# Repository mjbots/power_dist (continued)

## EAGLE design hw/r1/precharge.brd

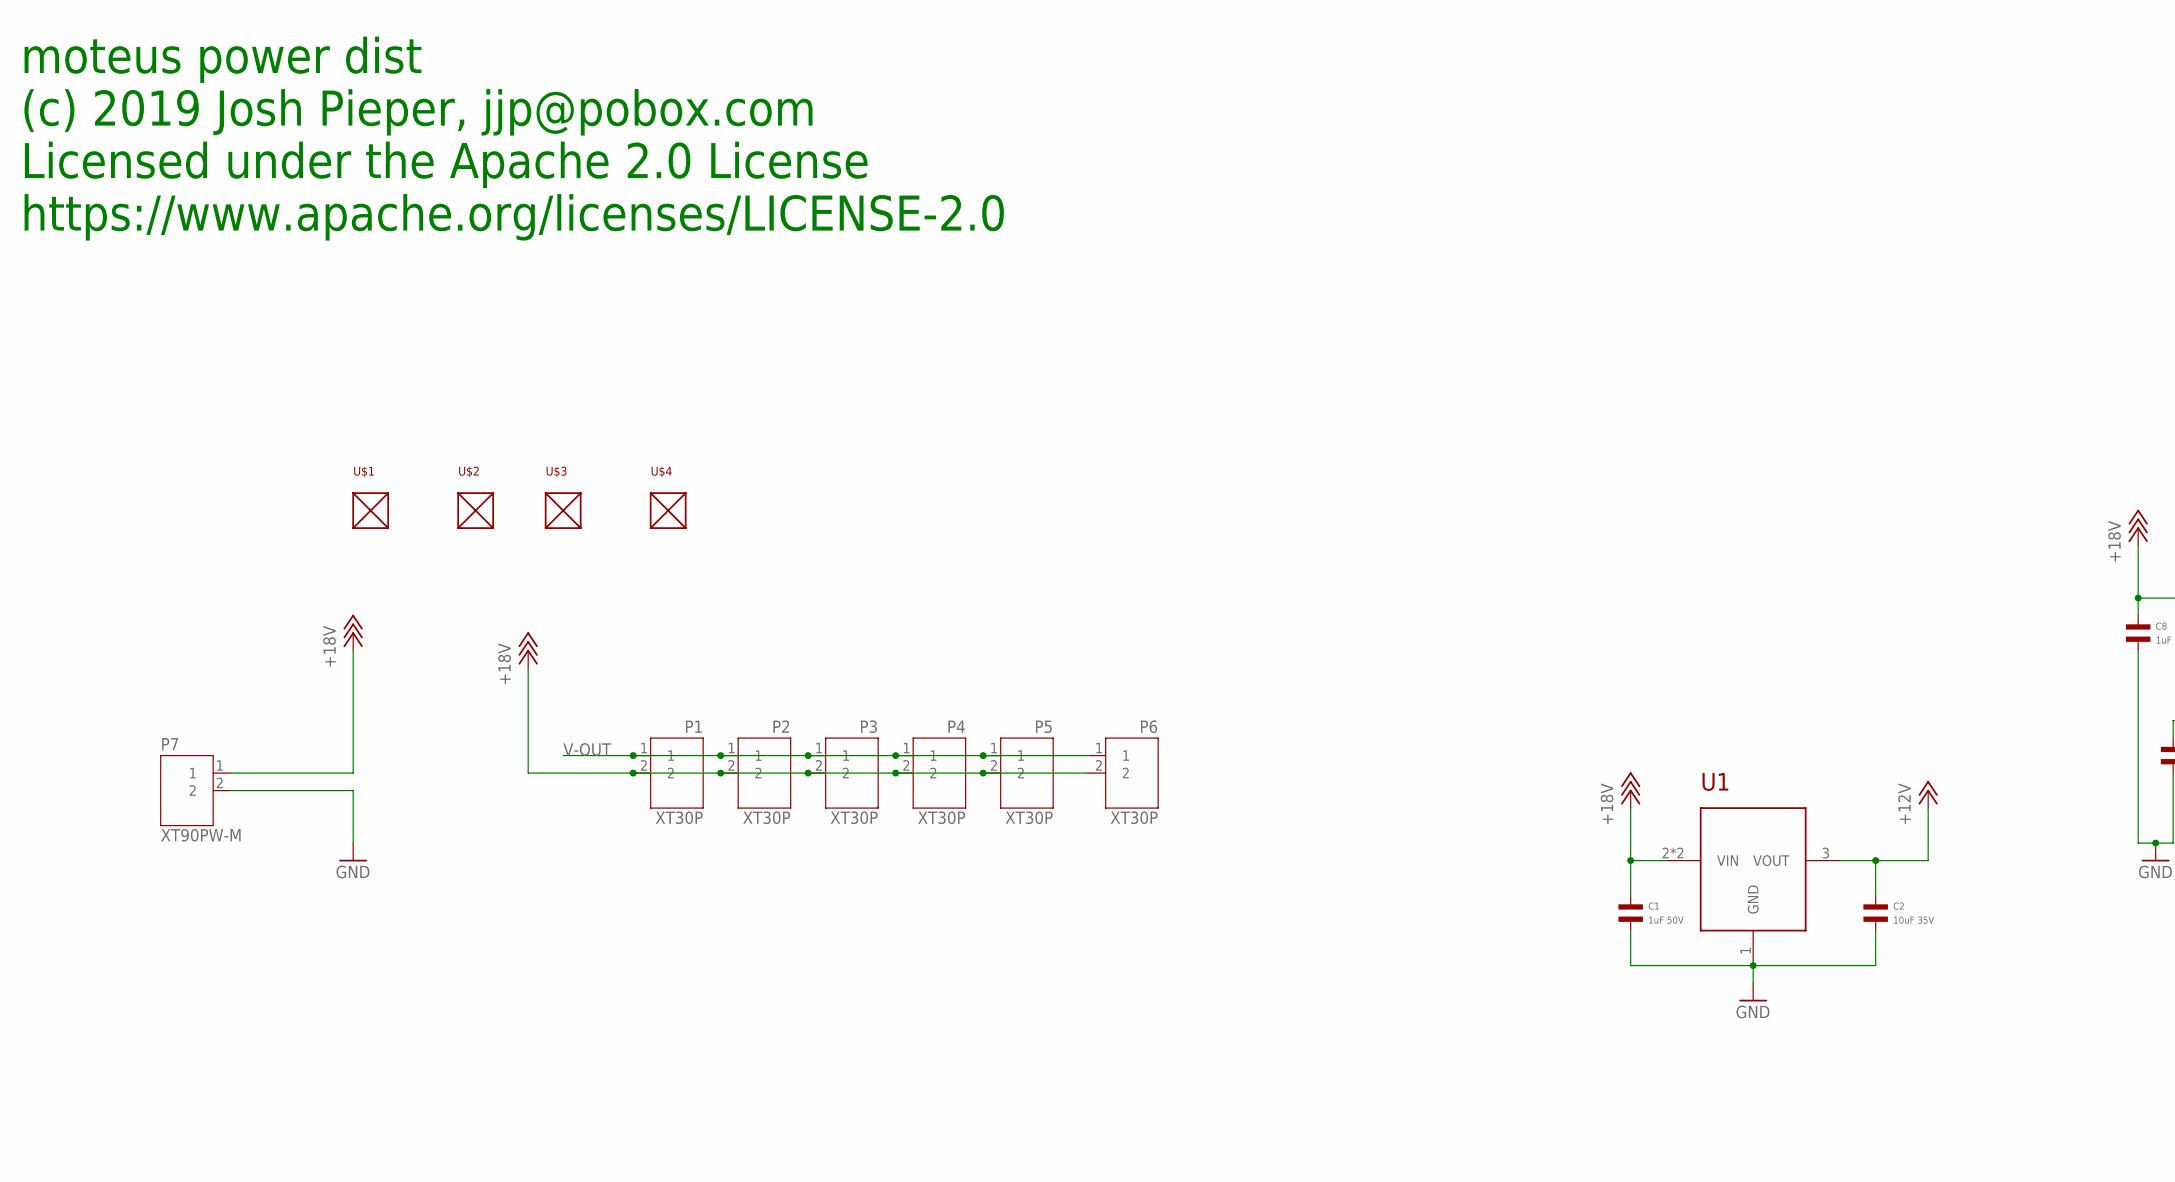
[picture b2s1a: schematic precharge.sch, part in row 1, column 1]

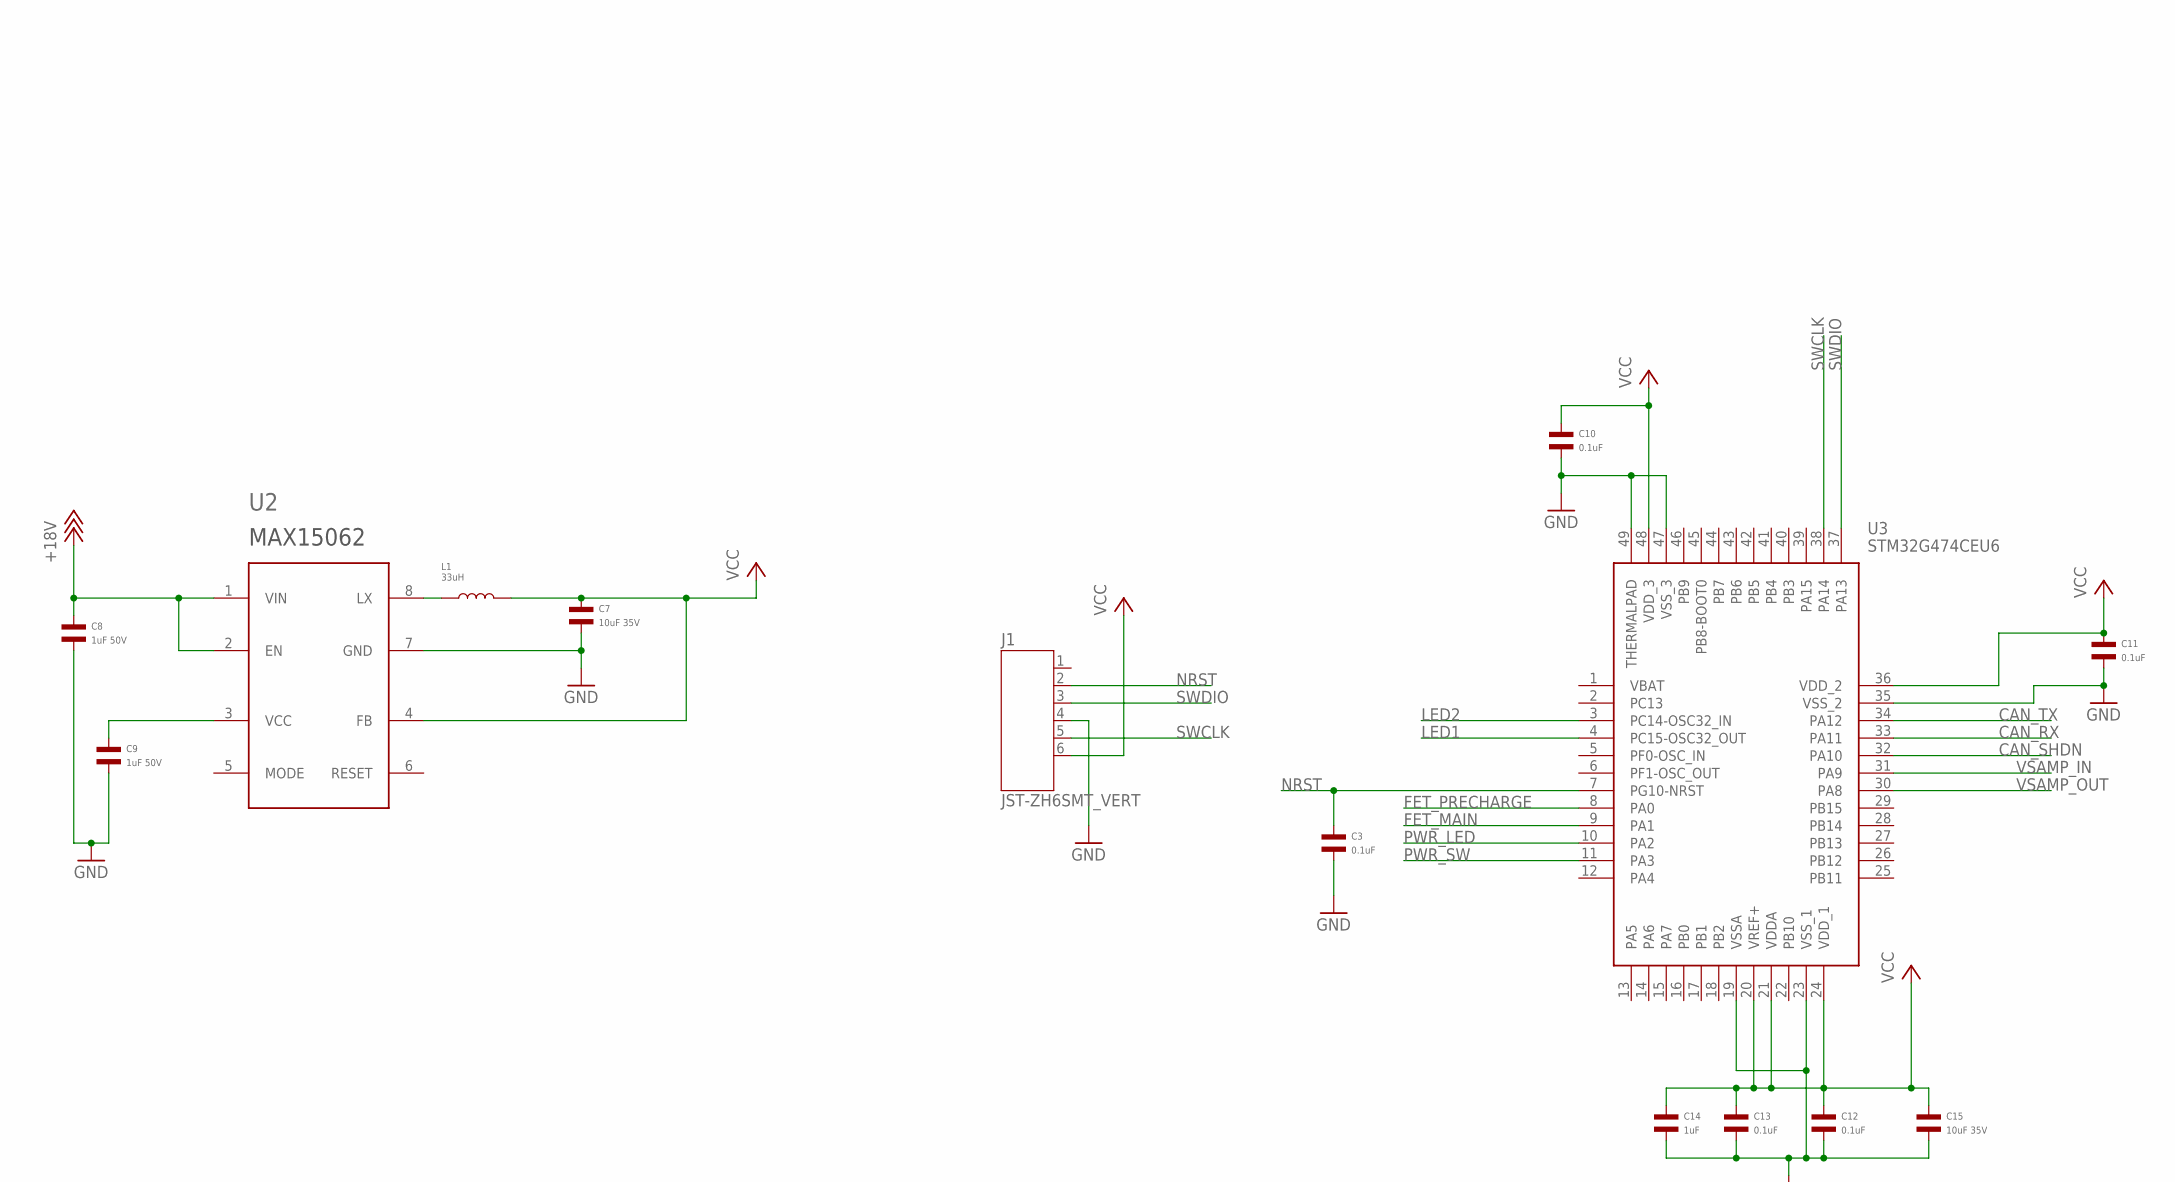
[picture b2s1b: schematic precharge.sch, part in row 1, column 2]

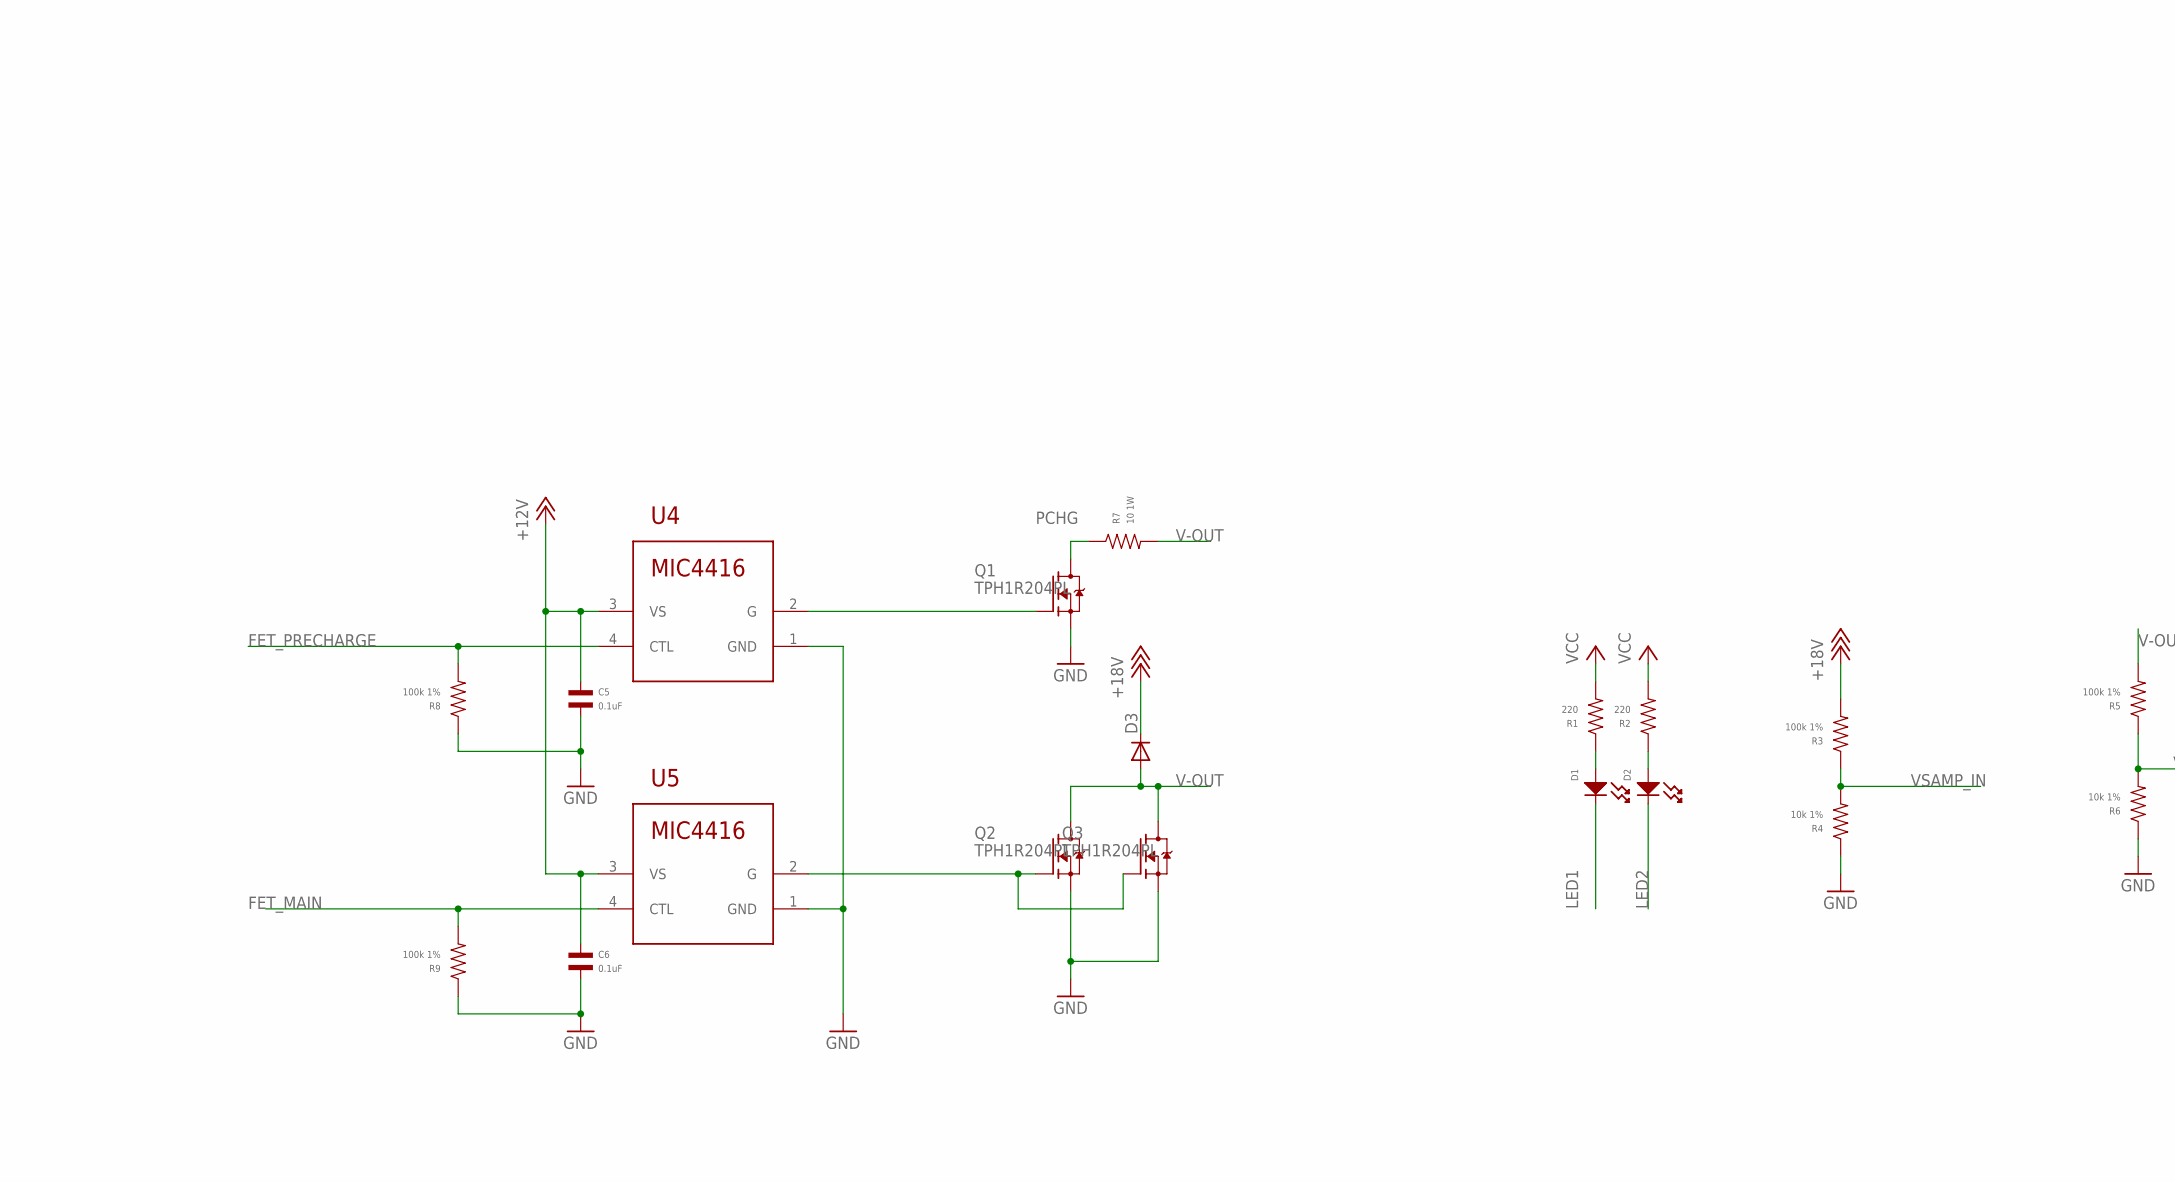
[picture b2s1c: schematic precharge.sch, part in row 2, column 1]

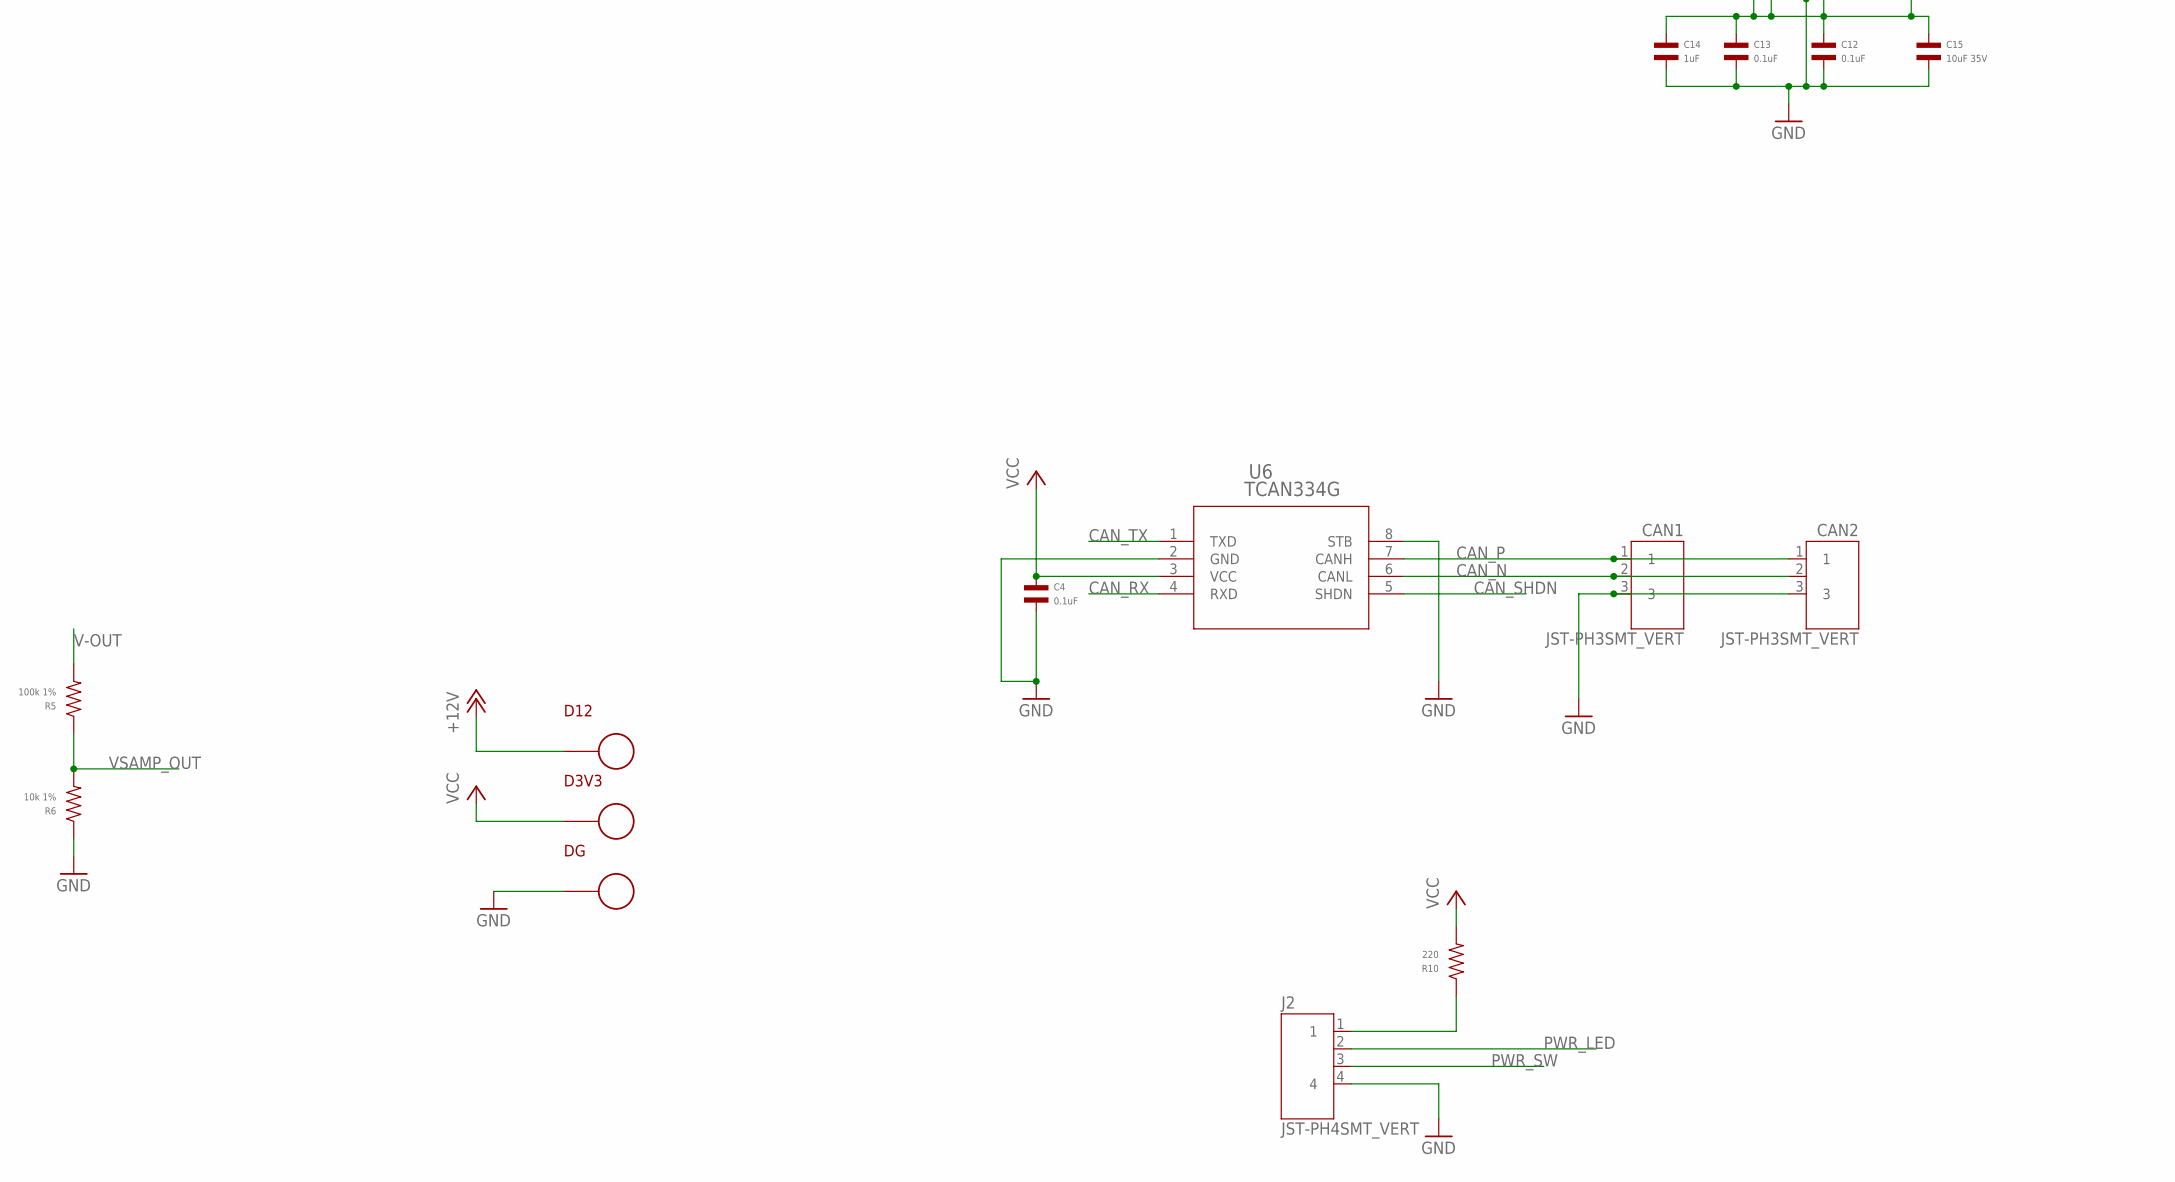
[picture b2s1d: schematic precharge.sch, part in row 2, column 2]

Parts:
C1, C8, C9: 1uF 50V; C0603; MPN CL10A105KB8NNNC
C2, C7, C15: 10uF 35V; C1206; MPN CGA5L1X7R1V106K160AC
C3, C4, C5, C6, C10, C11, C12, C13: 0.1uF; C0402; MPN MF-CAP-0402-0.1uF
C14: 1uF; C0402; MPN MF-CAP-0402-1uF
CAN1, CAN2: JST-PH3SMT_VERT; JST_B3B_PH-SM4-TB(LF)(SN); MPN B3B-PH-SM4-TB(LF)(SN)
D1, D2: LED_SINGLE-0603; LED0603; MPN MF-LED-0603-RED
D3: DIODE-; DO-214AB; MPN SK510L-TP
D3V3, D12: PAD24AWG_PAD; 24AWG_PAD
DG: PAD24AWG_PAD; 24AWG_PAD
J1: JST-ZH6SMT_VERT; JST_B6B-ZR-SM4-TF(LF)(SN); MPN B6B-ZR-SM4-TF(LF)(SN)
J2: JST-PH4SMT_VERT; JST_B4B_PH-SM4-TB(LF)(SN); MPN B4B-PH-SM4-TB(LF)(SN)
L1: 33uH; L1210; MPN NLFV32T-330K-EF
P1, P2, P3, P4, P5, P6: XT30P
P7: XT90PW-M
Q1, Q2, Q3: TPH1R204PL; SOP_ADVANCE; MPN TPH1R204PL,L1Q
R1, R2, R10: 220; R0603; MPN MF-RES-0603-220
R3, R5, R8, R9: 100k 1%; R0603; MPN CRCW0603100KFKEA
R4, R6: 10k 1%; R0603; MPN ERT-J1VG103FA
R7: 10 1W; R1206; MPN HRG3216Q-10R0-D-T1
U1: ZXTR2012Z; SOT89; MPN ZXTR2012Z-13
U2: MAX150628TDFN; 8TDFN; MPN MAX15062AATA+T
U3: STM32G474CEU6; QFN50P700X700X60-49N; MPN STM32G474CEU6
U4, U5: MIC4416; SOT143
U6: TCAN334G; SOT23-8; MPN TCAN334GDR
U$1, U$2, U$3, U$4: MOUNT; M2.5MOUNT

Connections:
+12V: C2.P$1, C5.P$1, C6.P$1, D12.P$1, U1.3 (VOUT), U4.3 (VS), U5.3 (VS)
+18V: C1.P$1, C8.P$1, D3.C, P1.2, P2.2, P3.2, P4.2, P5.2, P6.2, P7.1, R3.P$2, U1.2 (VIN), U1.PAD (VIN), U2.1 (VIN), U2.2 (EN)
CAN_N: CAN1.2, CAN2.2, U6.6 (CANL)
CAN_P: CAN1.1, CAN2.1, U6.7 (CANH)
CAN_RX: U3.33 (PA11), U6.4 (RXD)
CAN_SHDN: U3.32 (PA10), U6.5 (SHDN)
CAN_TX: U3.34 (PA12), U6.1 (TXD)
FET_MAIN: R9.P$2, U3.9 (PA1), U5.4 (CTL)
FET_PRECHARGE: R8.P$2, U3.8 (PA0), U4.4 (CTL)
GND: C1.P$2, C2.P$2, C3.P$2, C4.P$2, C5.P$2, C6.P$2, C7.P$2, C8.P$2, C9.P$2, C10.P$2, C11.P$2, C12.P$2, C13.P$2, C14.P$2, C15.P$2, CAN1.3, CAN2.3, DG.P$1, J1.4, J2.4, P7.2, Q1.1 (S), Q1.2 (S), Q1.3 (S), Q2.1 (S), Q2.2 (S), Q2.3 (S), Q3.1 (S), Q3.2 (S), Q3.3 (S), R4.P$1, R6.P$1, R8.P$1, R9.P$1, U1.1 (GND), U2.7 (GND), U3.19 (VSSA), U3.23 (VSS_1), U3.35 (VSS_2), U3.47 (VSS_3), U3.49 (THERMALPAD), U4.1 (GND), U5.1 (GND), U6.2 (GND), U6.8 (STB)
LED1: D1.CATHODE, U3.4 (PC15-OSC32_OUT)
LED2: D2.CATHODE, U3.3 (PC14-OSC32_IN)
LX: L1.P$1, U2.8 (LX)
unnamed: D1.ANODE, R1.P$1
unnamed: J2.1, R10.P$1
unnamed: Q2.4 (G), Q3.4 (G), U5.2 (G)
unnamed: D2.ANODE, R2.P$1
unnamed: Q1.4 (G), U4.2 (G)
unnamed: C9.P$1, U2.3 (VCC)
NRST: C3.P$1, J1.2, U3.7 (PG10-NRST)
PCHG: Q1.5 (D), Q1.6 (D), Q1.7 (D), Q1.8 (D), Q1.PAD (D), R7.P$1
PWR_LED: J2.2, U3.10 (PA2)
PWR_SW: J2.3, U3.11 (PA3)
SWCLK: J1.5, U3.38 (PA14)
SWDIO: J1.3, U3.37 (PA13)
V-OUT: D3.A, P1.1, P2.1, P3.1, P4.1, P5.1, P6.1, Q2.5 (D), Q2.6 (D), Q2.7 (D), Q2.8 (D), Q2.PAD (D), Q3.5 (D), Q3.6 (D), Q3.7 (D), Q3.8 (D), Q3.PAD (D), R5.P$2, R7.P$2
VCC: C4.P$1, C7.P$1, C10.P$1, C11.P$1, C12.P$1, C13.P$1, C14.P$1, C15.P$1, D3V3.P$1, J1.6, L1.P$2, R1.P$2, R2.P$2, R10.P$2, U2.4 (FB), U3.20 (VREF+), U3.21 (VDDA), U3.24 (VDD_1), U3.36 (VDD_2), U3.48 (VDD_3), U6.3 (VCC)
VSAMP_IN: R3.P$1, R4.P$2, U3.31 (PA9)
VSAMP_OUT: R5.P$1, R6.P$2, U3.30 (PA8)

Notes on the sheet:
moteus power dist (c) 2019 Josh Pieper, jjp@pobox.com Licensed under the Apache 2.0 License https://www.apache.org/licenses/LICENSE-2.0

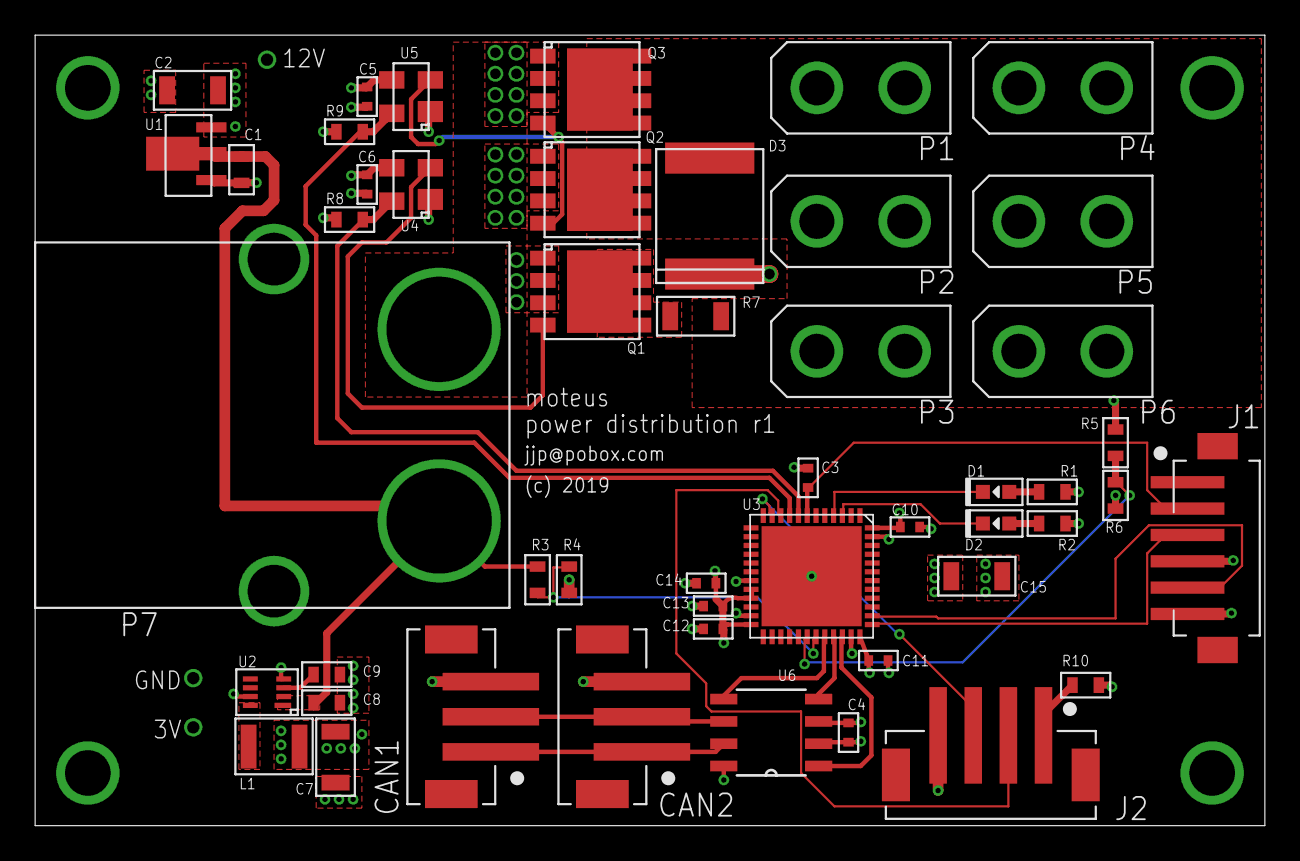
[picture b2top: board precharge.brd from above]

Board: 4 copper layers, 70.0 x 45.0 mm, 56 parts (0 on the bottom side), 29 nets.

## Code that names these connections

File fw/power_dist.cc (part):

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    HAL_GPIO_Init(GPIOA, &init);
  }

  // ISAMP_BIAS is PA4 -> DAC1_OUT1
  DAC1->MCR = (
      (0 << DAC_MCR_HFSEL_Pos) | // High frequency mode disabled
      (0 << DAC_MCR_MODE1_Pos) | // external pin with buffer enabled
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  };

  PowerDist() :
      gpio1_(GPIO1, 1),
      gpio2_(GPIO2, 0),
      can_shdn_(CAN_SHDN, 0),
      can_([&]() {
             fw::FDCan::Options options;
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
  void SetupAnalog() {
    // Analog Mappings:
    //  VSAMP_OUT -> PA7 -> OPAMP1_VINP -> ADC1/IN13
    //  VSAMP_IN -> PB14 -> OPAMP2_VINP -> ADC2/IN16
    //  FET_TEMP -> PC5 -> ADC2/IN5
    //  ISAMP -> PB0 -> OPAMP3 -> PB1 -> ADC3/IN1 -> PB15 -> OPAMP5 -> PA8 -> ADC5/IN1
    //  DAC1 -> PA4 -> ISAMP_BIAS -> PA1 -> ADC12_IN2
    //  DAC3 -> internal
    //  DAC4 -> internal -> OPAMP5/VINP
    //  Internal_TEMP -> ADC5/IN4
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    (void) isamp_in_raw;
    const uint16_t isamp_in = ADC5->DR;

    const float vsamp_out =
        static_cast<float>(vsamp_out_raw) / 4096.0f * 3.3f / vsamp_divide_;
    const float vsamp_in =
        static_cast<float>(vsamp_in_raw) / 4096.0f * 3.3f / vsamp_divide_;
    const float V_per_A = config_.current_sense_ohm * 8 * 7;
    const float isamp =
        -((static_cast<float>(isamp_in) -
           status_.isamp_offset) / 4096.0f * 3.3f) / V_per_A;

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        (static_cast<float>(int_temp_raw) - ts_cal1_) / static_cast<float>(ts_cal2_ - ts_cal1_) * 100.0f + 30.0f;

    if (vsamp_out > 4.0f) {
      const float delta_energy_uW_hr = vsamp_in * isamp * 0.001f / 3600.0f * 1e6f;
      status_.energy_uW_hr += static_cast<int32_t>(delta_energy_uW_hr);
    }

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  DigitalOut override_3v3_{OVERRIDE_3V3, 1};


  OpAmpBuffer opamp1_{OPAMP1, 2};  // PA7 == VINP2
  OpAmpBuffer opamp2_{OPAMP2, 1};  // PB14 == VINP1
  OpAmpBuffer opamp3_{OPAMP3, 0, OpAmpBuffer::kExternal};  // PB0 == VINP0, output = PB1
  OpAmpInvertingAmplifier opamp5_{OPAMP5};  // PB15 == VINM0

  Config config_;
  Status status_;
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
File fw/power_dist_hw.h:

// Copyright 2023 mjbots Robotic Systems, LLC.  info@mjbots.com
//
// Licensed under the Apache License, Version 2.0 (the "License");
// you may not use this file except in compliance with the License.
// You may obtain a copy of the License at
//
//     http://www.apache.org/licenses/LICENSE-2.0
//
// Unless required by applicable law or agreed to in writing, software
// distributed under the License is distributed on an "AS IS" BASIS,
// WITHOUT WARRANTIES OR CONDITIONS OF ANY KIND, either express or implied.
// See the License for the specific language governing permissions and
// limitations under the License.

#pragma once

// r2 and r3 silk is hw rev 0
// r4.0, r4.1 silk is hw rev 1
// r4.2 is hw rev 2, but is undistributed
// r4.3, r4.3b, r4.4 is hw rev 2
// r4.5 is hw rev 3

namespace fw {

extern volatile uint8_t g_measured_hw_rev;

}

// The most recent version of the HW.
#ifndef POWER_DIST_HW_REV
// r4.3b silk
#define POWER_DIST_HW_REV 2
#endif

constexpr int kHardwareInterlock[] = {
  0,   // r2, r3
  1,   // r4.0, r4.1
  2,   // r4.3, r4.3b, r4.4
  3,   // r4.5
};

// This firmware is compatible with the following hardware revisions.
constexpr int kCompatibleHwRev[] = {
  2, 3
};

#define HWREV_PIN0 PC_6
#define HWREV_PIN1 PA_15
#define HWREV_PIN2 PC_13

#define DEBUG_LED1 PA_0
#define DEBUG_LED2 PA_1

#define PWR_LED PB_12
#define PWR_SW PA_2

#define VSAMP_IN PB_14
#define VSAMP_OUT PA_7

#define CAN_TX PA_12
#define CAN_RX PA_11
#define CAN_SHDN PA_10


#define GPIO1 PC_10
#define GPIO2 PC_11
#define GPIO3 PB_3

#define ISAMP_BIAS PA_4
#define ISAMP PB_0
#define ISAMP_BUF_OUT PB_1
#define ISAMP_BUF_IN PB_15
#define ISAMP_AMP PA_8
#define OVERRIDE_PWR PC_14
#define OVERRIDE_3V3 PB_13
#define TPS2490_FLT PA_5
#define TSP2490_TIMER PB_11
#define FET_TEMP PC_5

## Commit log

2020-12-02 Initial port of sw
2020-12-02 Travis files
2020-12-02 Get license in here
2020-12-02 Hardware designs
2020-12-02 A top level build file
2020-12-07 Work towards functioning r4
    * Beginnings of firmware
    * Initial README and CHANGES
    * Start on r4.1 w/ fixed D3 footprint
2020-12-09 Hack enough stuff in to get tview working
2020-12-09 Fix inconsistency in schematic
2020-12-10 Initial stub of LM5066 support
    This seems to be able to read and report data, and at least input
    voltage seems reasonable.
    tview does seem to become corrupted frequently, possibly related to
    the CAN status spamming.
2020-12-11 Update default bitrate to 1000000
2020-12-11 Calibrate reported current and power
2020-12-12 Document why we configure the lm5066 the way we do
2020-12-12 Fix the git version
    I just neglected to update the namespace in the linkstamp file
2020-12-12 Implement minimal reporting of lm5066 faults
2020-12-12 Turn off retries
2020-12-13 Draft r4.1 based on the LTC4380
2020-12-13 Connect GND/PGND and fix XT90 TH size
2020-12-13 Resize and draft place all silks
2020-12-14 Rename all resistors, capacitors, and diodes
2020-12-14 Fine place silks
2020-12-14 Fix a few minor glitches
2020-12-14 Fix more minor layout and naming glitches
2020-12-14 Add more debugging pads
2020-12-14 More debug pad position tweaks
2020-12-21 r4.1 design files
2020-12-21 Switch to 0.5mohm sense resistor and full voltage range
2020-12-21 Report input voltage over CAN
2020-12-22 Recover from BusOff and once again handle commands
2020-12-23 Capture remaining r4.1 artifacts
2020-12-23 Rough placement of r4.2 with the TPS2490
2020-12-23 r4.2 everything rough routed
2020-12-23 Connect TIMER to an ADC and add a FET temperature sensor
2020-12-23 Renumber all resistors and caps
2020-12-23 Place all silks and add a few more debug points
2021-01-05 Beginnings of making fw work on r4.1
2021-01-05 Get vsamp_in/out working through the opamp buffers
2021-01-05 Get ISAMP_BIAS DAC to work
2021-01-06 Kinda get current sampling to work, although scaling isn't right
2021-01-06 WIP: Attempt unsuccessfully to get current sensing working on r4.1
    This moves the input to PB0 to be buffered by OPAMP3 before being
    amplified by OPAMP6. The amplification appears to be not working, and
    I'm not 100% sure the buffering is working either.
2021-01-07 WIP which actually senses current with amplification
2021-01-08 Finish proving out r4.1 functionality
2021-01-08 Incorporate r4.1 feedback
2021-01-08 Tweak silks and layouts, set isolate for all power nets
2021-01-08 Fine silk placement
2021-01-08 Slight silk tweak
2021-01-10 Capture r4.2 as sent for mf
2021-01-10 Update the solder mask to be more amenable to oshstencil
2021-01-17 Fix a part number
2021-01-19 Minimal updates for r4.2, add decode script
2021-01-20 More work on r4.2 firmware
2021-01-20 Update to r4.3 wiring, add fet temp support
2021-01-20 Start on r4.3
    This version dispenses with all the latching junk for main power, just
    leaving it for the 3.3V rail. Now, the stm32 is completely
    responsible for turning the main power on and off, which could allow
    it to reset the hot swap controller if need be.
2021-01-20 Switch the LTC1787 filter to a 0.1uF
2021-01-22 Updates for r4.3
2021-01-22 Implement an actual state machine and report more values over CAN
2021-01-22 Move some wires further apart
    Reduce the paste fill ratio under the stm32
2021-01-22 Minor position tweaks after gerber viewing
2021-01-24 Capture r4.3
2021-02-13 Add part numbers, rev to 4.3b
2021-03-02 Port reference documentation over
2021-03-02 Increase the pre-charging timeout
2021-03-02 Capture r4.3b
2021-03-02 Remove most firmware support for silk r3.x boards
2021-03-02 Restructure to be slightly more maintainable
    Now we actually have reasonably sized functions, and expose all data
    through a multiplex telemetry protocol. Still necessary are an actual
    register based protocol, and diagnostic mode commands.
2021-03-02 Implement a register based protocol
2021-03-02 Update docs for r4.3b with register based protocol
2021-03-02 Include build timestamp in firmware image
2021-03-02 Default ID to 32
2021-03-02 Add a diagnostic console way to set the switch lock time
2021-03-02 Actually make reading energy via registers work
2021-03-02 Actually obey the lock time!
2021-03-04 Report the serial number over telemetry
2021-04-07 Include mechanical drawings and models for 4.3b
2021-04-19 Document alternate default ID
2021-06-05 Support recording device uuid
2021-06-05 Support 16 bit lock times
2021-06-06 Fix typos in doc
2021-06-06 Update flashing script and documentation
2021-06-06 Improve flashing docs
2022-11-04 Rev to use a staged 5V, then 3.3V regulator
    This way we have a 300mA 5V supply on board to use with a beefier CAN
    transceiver
2022-11-04 Switch to a 5V CAN transceiver
    Add enough 0 ohms and DNPs to support populating with a 3.3V native
    transceiver as well.
2022-11-04 Minor improvements
    * Add a 5V debug pad
    * Tweak routing and silks
2022-11-07 Tweak some silks
2022-11-07 Switch the 27nF cap to one that exists
2022-11-23 Fix TVS diode footprint
2022-12-16 Update bazel_deps
2022-12-16 Enable CAN transceiver delay compensation
2022-12-22 Reroute the regulators and lots of power things
    Try to improve the grounding and decoupling for the buck converters.
    Add some more decoupling caps and place them so as to hopefully reduce
    the amount of ground bounce noise that was interfering with current
    sensing.
2022-12-22 Add a lot more vias
2022-12-23 More tweaks
2022-12-23 Set the ADC prescaler, support r4.5 boards
2022-12-23 Capture r4.4
2022-12-23 More layout and silk tweaks
2022-12-23 Switch PGND to the regulators to be a fill instead of trace
2022-12-23 r4.5 as sent to mfg
2022-12-28 Switch the XT90 drills from 3.7 to 3.9mm
2022-12-31 Final version sent for mf
2023-01-24 Bump version to 4.5b
    Scoot the input regulators around to give the 5V inductor more room
2023-01-24 Improve noise in the power subsystem
    * Replace the 3.3V regulator with a linear one
    * The inductor is just swapped for a shunt, so that the switcher
    could be put back in for testing
    * Increase the 5V regulator input capacitance to 4.7uF from 1uF
    * Shift a bunch of stuff around to make room for the bigger cap
2023-01-24 Connect the grounds on both sides of the 3V regulator
2023-01-27 Attempt to make the isamp capturing be more robust
2023-05-18 * Make the current sense resistor configurable * Provide a diagnostic channel means of forcing the output on/off
2023-05-18 Capture r4.5b
2023-08-17 Update to bazel 5.4.1
    Update deps while we're at it
2023-09-25 Update all copyrights to be mjbots
2024-02-05 Update "most recent" for power_dist documentation
2024-04-03 When we upgraded mjlib, it required a new Poll operation
    Somehow this managed to evade local testing. Without it, the firmware
    does not respond to most, if any, CAN communication.
    Follow up to 4c13a583a957ac7d6b0ae2fe4c5564305a949752
2024-04-03 Provide a configurable mechanism to disable sleeping
2024-05-22 Create two examples showing how to access the power_dist data with python
2024-07-10 Wait a bit before sampling the version pins
2024-07-10 Move all the power_dist board files into their own subdirectory
2024-07-10 Remove legacy board files
2024-09-05 mjpower-ss
    New board, largely same functionality as power_dist.
    + onboard switch
    + smaller size (50x70mm vs 50x80mm)
    + design files in KiCAD
    - CAN-FD monitoring and soft-switch lockout
    Still has:
2024-09-05 Update documentation for mjpower-ss
2025-01-04 Update bazel_deps and mjlib
2025-01-04 Upgrade to bazel 7.4.1
2025-09-29 Support OTP UUID and modern CAN addressing
    This updates power_dist to match moteus in terms of support UUID based
    addressing over CAN. The UUID can now be set in the OTP. UUID
    addressing is supported, and hardware CAN filters are used to only
    receive things that are actually destined for us.
2025-09-29 Add a tool to make release images
2025-11-30 Update mjlib and rules_mbed dependencies
2025-12-01 Fix CAN-FD communication
    Follow up to 8a68840a64530206a1917cc91bbe746aeba026e8
    1. We accidentally turned off delay compensation, which is necessary
    to actually transmit.
    2. Automatic retransmission should be enabled, to match other
    peripheral devices like moteus.
2025-12-16 Update documentation to match actual firmware
